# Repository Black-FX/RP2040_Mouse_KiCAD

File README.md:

# RP2040_Mouse_KiCAD
This is the hardware side of an RP2040 USB to Quadrature mouse adaptor used with retro computers, the software is available at https://github.com/Black-FX/RP2040_Mouse

A PDF of the scematic is available in [Here](PDF/scematic.pdf)

Glamour shots

# Ordering

You can order the boards here:

[PCBWay](https://www.pcbway.com/project/shareproject/RP2040_USB_Mouse_to_Quadrature_15de42f1.html)

I sell pre-assembled and programmed ones here:

[Tindie](https://www.tindie.com/products/darrens_lab/rp2040-usb-to-quadrature-mouse-adaptor/)

[EBay](https://www.ebay.com/usr/darrens_lab_nz?_trksid=p2047675.m145687.l151929)

[Trademe NZ & Aus](https://www.trademe.co.nz/a/search?member_listing=7404797&bof=McH9Ulww)

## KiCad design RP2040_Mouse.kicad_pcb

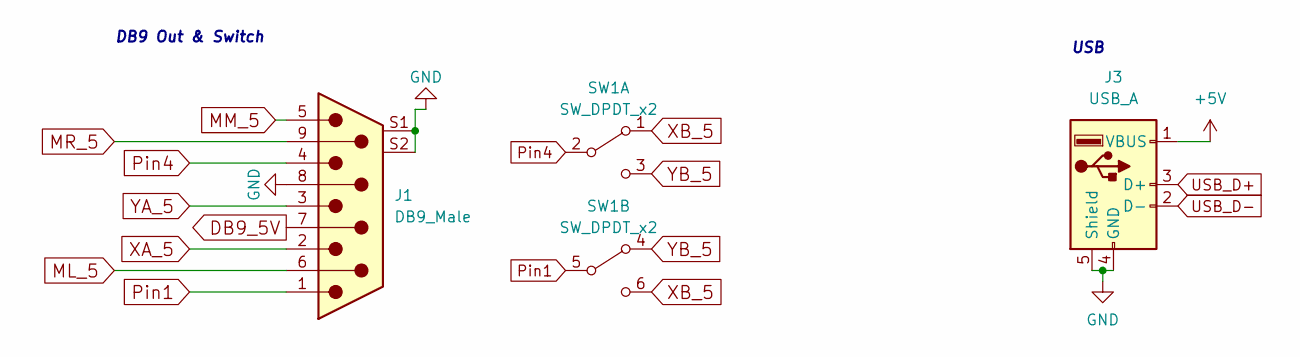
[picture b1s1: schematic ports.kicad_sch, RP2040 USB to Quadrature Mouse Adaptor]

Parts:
J1: DB9_Male; ASSMANN_A-DF_09_A_KG-T2S
J3: USB_A; USB_A_China
SW1: SW_DPDT_x2; SW_DPDT_CK_JS202011JCQN

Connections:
+5V: J3.1 (VBUS); also elsewhere on the board
DB9_5V: J1.7; also elsewhere on the board
GND: J1.8, J1.S1, J1.S2, J3.4 (GND), J3.5 (Shield); also elsewhere on the board
ML_5: J1.6; also elsewhere on the board
MM_5: J1.5; also elsewhere on the board
MR_5: J1.9; also elsewhere on the board
Pin1: J1.1, SW1.5 (B)
Pin4: J1.4, SW1.2 (B)
USB_D+: J3.3 (D+); also elsewhere on the board
USB_D-: J3.2 (D-); also elsewhere on the board
XA_5: J1.2; also elsewhere on the board
XB_5: SW1.1 (A), SW1.6 (C); also elsewhere on the board
YA_5: J1.3; also elsewhere on the board
YB_5: SW1.3 (C), SW1.4 (A); also elsewhere on the board

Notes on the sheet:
USB
DB9 Out & Switch

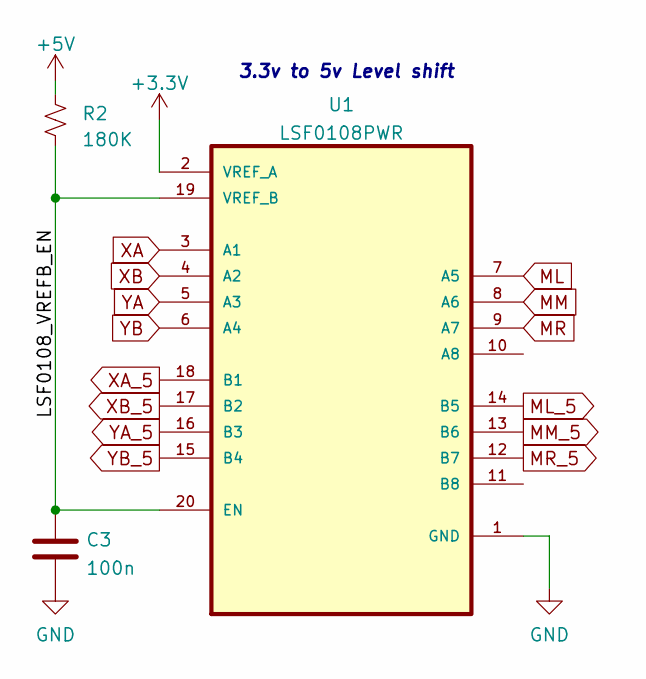
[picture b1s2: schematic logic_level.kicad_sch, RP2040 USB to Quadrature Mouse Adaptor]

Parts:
C3: 100n; C_0402_1005Metric
R2: 180K; R_0402_1005Metric
U1: LSF0108PWR; TSSOP-20_4.4x6.5mm_P0.65mm

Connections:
+3V3: U1.2 (VREF_A); also elsewhere on the board
+5V: R2.1; also elsewhere on the board
/Logic Level Shift/LSF0108_VREFB_EN: C3.1, R2.2, U1.19 (VREF_B), U1.20 (EN)
GND: C3.2, U1.1 (GND); also elsewhere on the board
ML: U1.7 (A5); also elsewhere on the board
ML_5: U1.14 (B5); also elsewhere on the board
MM: U1.8 (A6); also elsewhere on the board
MM_5: U1.13 (B6); also elsewhere on the board
MR: U1.9 (A7); also elsewhere on the board
MR_5: U1.12 (B7); also elsewhere on the board
XA: U1.3 (A1); also elsewhere on the board
XA_5: U1.18 (B1); also elsewhere on the board
XB: U1.4 (A2); also elsewhere on the board
XB_5: U1.17 (B2); also elsewhere on the board
YA: U1.5 (A3); also elsewhere on the board
YA_5: U1.16 (B3); also elsewhere on the board
YB: U1.6 (A4); also elsewhere on the board
YB_5: U1.15 (B4); also elsewhere on the board

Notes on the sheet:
3.3v to 5v Level shift

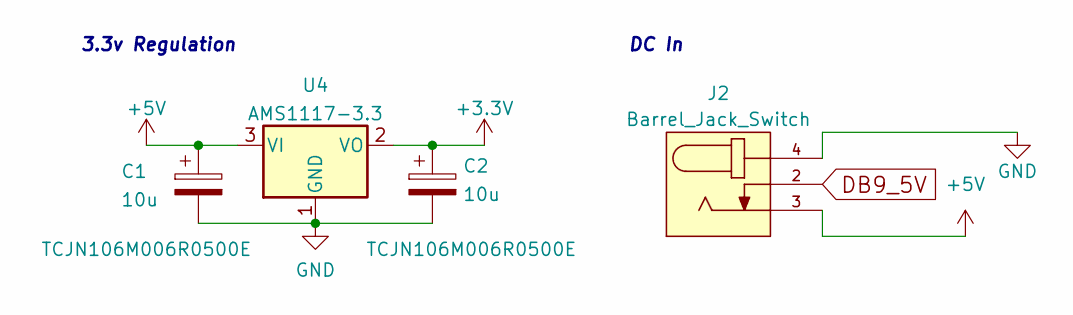
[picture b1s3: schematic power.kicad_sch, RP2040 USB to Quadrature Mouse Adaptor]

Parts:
C1, C2: 10u; C_0805_2012Metric; Part TCJN106M006R0500E
J2: Barrel_Jack_Switch; NINIGI_DC-005
U4: AMS1117-3.3; SOT-223-3_TabPin2

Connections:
+3V3: C2.1, U4.2 (VO); also elsewhere on the board
+5V: C1.1, J2.3, U4.3 (VI); also elsewhere on the board
DB9_5V: J2.2; also elsewhere on the board
GND: C1.2, C2.2, J2.4, U4.1 (GND); also elsewhere on the board

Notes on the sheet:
3.3v Regulation
DC In

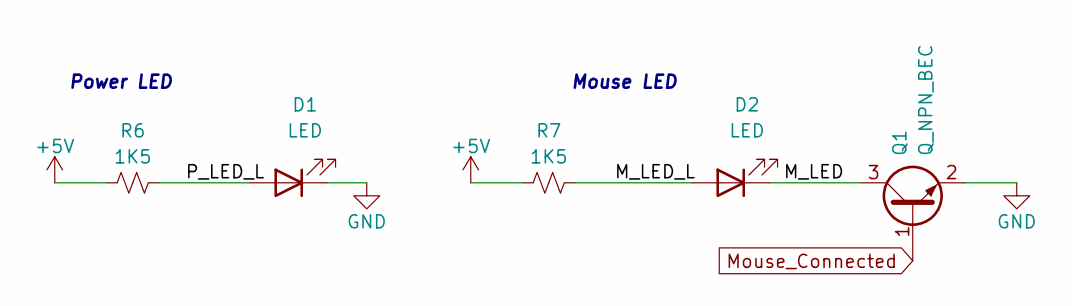
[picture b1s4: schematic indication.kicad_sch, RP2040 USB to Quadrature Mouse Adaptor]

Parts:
D1, D2: LED; LED_0603_1608Metric
Q1: Q_NPN_BEC; SOT-23-3
R6, R7: 1K5; R_0402_1005Metric

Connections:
+5V: R6.1, R7.1; also elsewhere on the board
/Indication/M_LED: D2.1 (K), Q1.3 (C)
/Indication/M_LED_L: D2.2 (A), R7.2
/Indication/P_LED_L: D1.2 (A), R6.2
GND: D1.1 (K), Q1.2 (E); also elsewhere on the board
Mouse_Connected: Q1.1 (B); also elsewhere on the board

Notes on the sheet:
Mouse LED
Power LED

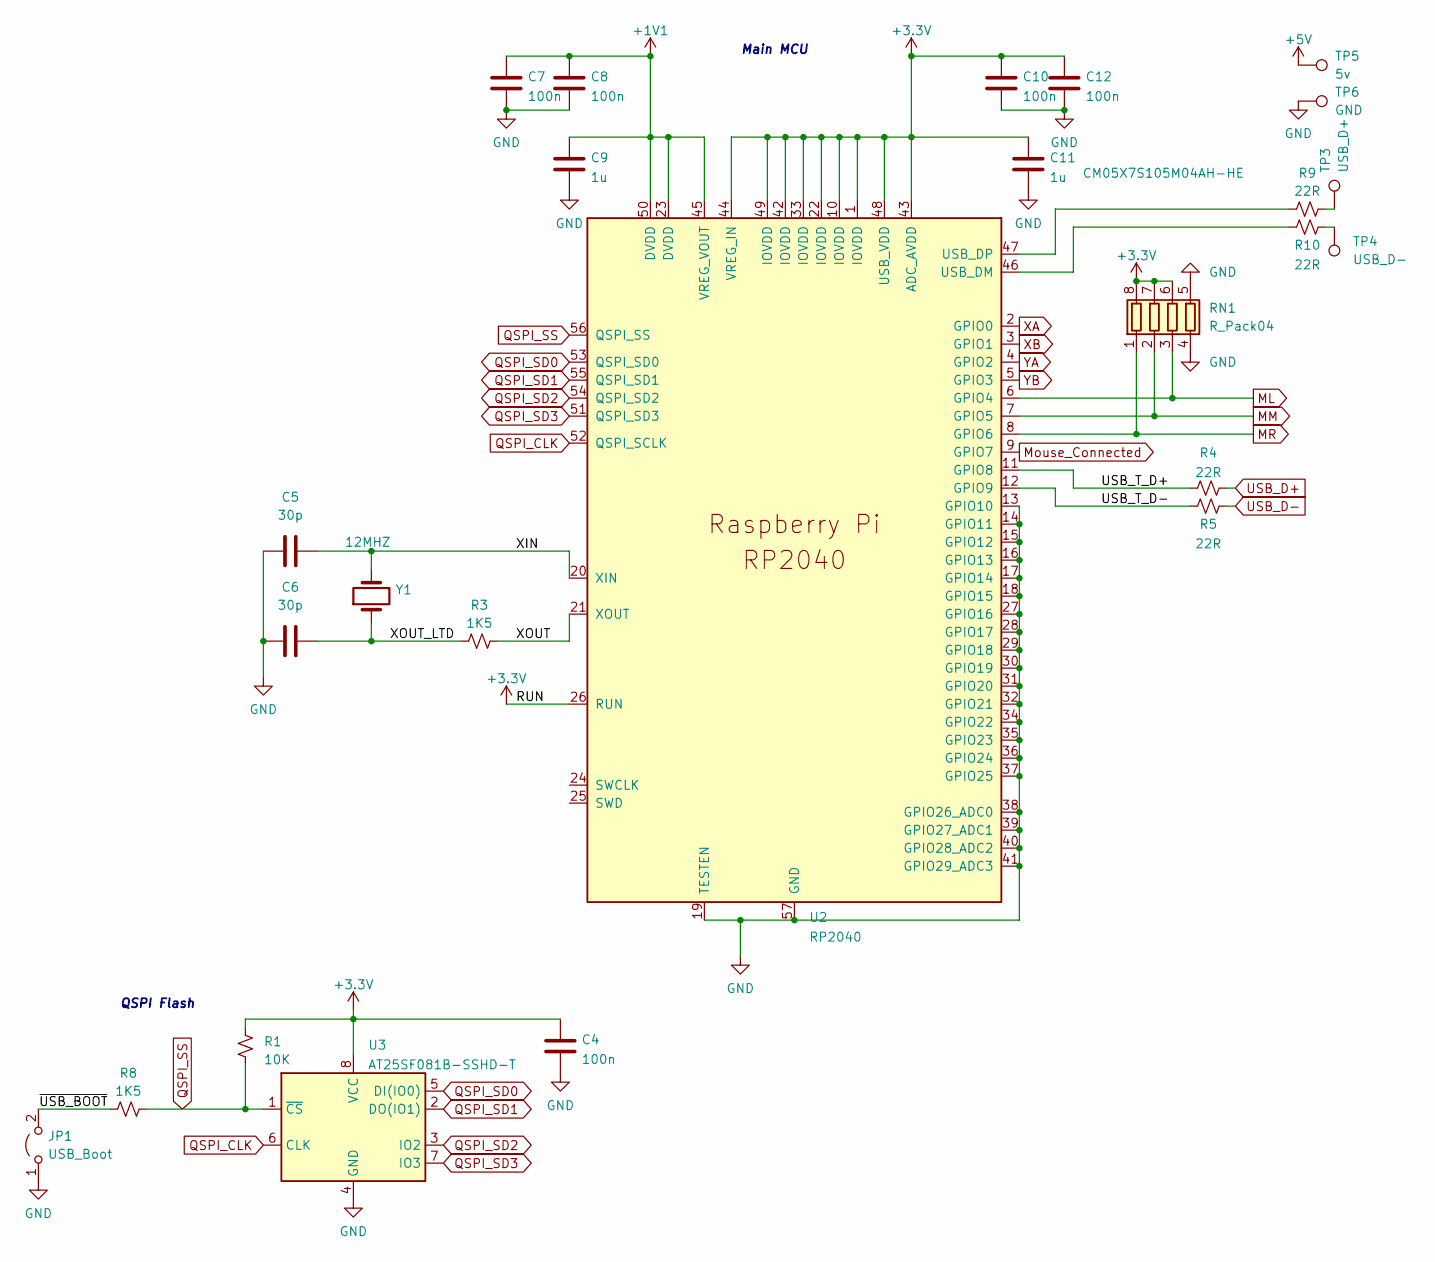
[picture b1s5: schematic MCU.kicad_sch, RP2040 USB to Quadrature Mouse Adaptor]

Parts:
C4, C7, C8, C10, C12: 100n; C_0402_1005Metric
C5, C6: 30p; C_0402_1005Metric
C9: 1u; C_0402_1005Metric
C11: 1u; C_0402_1005Metric; Part CM05X7S105M04AH-HE
JP1: USB_Boot; PinHeader_1x02_P1.27mm_Vertical
R1: 10K; R_0402_1005Metric
R3, R8: 1K5; R_0402_1005Metric
R4, R5, R9, R10: 22R; R_0402_1005Metric
RN1: R_Pack04; R_Array_Concave_4x0402
TP3: USB_D+; TestPoint_Pad_D1.0mm
TP4: USB_D-; TestPoint_Pad_D1.0mm
TP5: 5v; TestPoint_Pad_D1.0mm
TP6: GND; TestPoint_Pad_D1.0mm
U2: RP2040; RP2040-QFN-56
U3: AT25SF081B-SSHD-T; SOIC-8-1EP_3.9x4.9mm_P1.27mm_EP2.29x3mm
Y1: 12MHZ; Crystal_SMD_5032-2Pin_5.0x3.2mm

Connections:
+1V1: C7.1, C8.1, C9.1, U2.23 (DVDD), U2.45 (VREG_VOUT), U2.50 (DVDD)
+3V3: C4.1, C10.1, C11.1, C12.1, R1.1, RN1.6 (R3.2), RN1.7 (R2.2), RN1.8 (R1.2), U2.1 (IOVDD), U2.10 (IOVDD), U2.22 (IOVDD), U2.26 (RUN), U2.33 (IOVDD), U2.42 (IOVDD), U2.43 (ADC_AVDD), U2.44 (VREG_IN), U2.48 (USB_VDD), U2.49 (IOVDD), U3.8 (VCC); also elsewhere on the board
+5V: TP5.1; also elsewhere on the board
/Microcontroller/USB_T_D+: R4.1, U2.11 (GPIO8)
/Microcontroller/USB_T_D-: R5.2, U2.12 (GPIO9)
/Microcontroller/XIN: C5.2, U2.20 (XIN), Y1.2
/Microcontroller/XOUT: R3.2, U2.21 (XOUT)
/Microcontroller/XOUT_LTD: C6.2, R3.1, Y1.1
/Microcontroller/~USB_BOOT: JP1.2 (B), R8.1
GND: C4.2, C5.1, C6.1, C7.2, C8.2, C9.2, C10.2, C11.2, C12.2, JP1.1 (A), RN1.4 (R4.1), RN1.5 (R4.2), TP6.1, U2.13 (GPIO10), U2.14 (GPIO11), U2.15 (GPIO12), U2.16 (GPIO13), U2.17 (GPIO14), U2.18 (GPIO15), U2.19 (TESTEN), U2.27 (GPIO16), U2.28 (GPIO17), U2.29 (GPIO18), U2.30 (GPIO19), U2.31 (GPIO20), U2.32 (GPIO21), U2.34 (GPIO22), U2.35 (GPIO23), U2.36 (GPIO24), U2.37 (GPIO25), U2.38 (GPIO26_ADC0), U2.39 (GPIO27_ADC1), U2.40 (GPIO28_ADC2), U2.41 (GPIO29_ADC3), U2.57 (GND), U3.4 (GND); also elsewhere on the board
ML: RN1.3 (R3.1), U2.6 (GPIO4); also elsewhere on the board
MM: RN1.2 (R2.1), U2.7 (GPIO5); also elsewhere on the board
MR: RN1.1 (R1.1), U2.8 (GPIO6); also elsewhere on the board
Mouse_Connected: U2.9 (GPIO7); also elsewhere on the board
unnamed: R9.2, TP3.1
unnamed: R10.1, TP4.1
unnamed: R10.2, U2.46 (USB_DM)
unnamed: R9.1, U2.47 (USB_DP)
QSPI_CLK: U2.52 (QSPI_SCLK), U3.6 (CLK)
QSPI_SD0: U2.53 (QSPI_SD0), U3.5 (DI(IO0))
QSPI_SD1: U2.55 (QSPI_SD1), U3.2 (DO(IO1))
QSPI_SD2: U2.54 (QSPI_SD2), U3.3 (IO2)
QSPI_SD3: U2.51 (QSPI_SD3), U3.7 (IO3)
QSPI_SS: R1.2, R8.2, U2.56 (QSPI_SS), U3.1 (~CS)
USB_D+: R4.2; also elsewhere on the board
USB_D-: R5.1; also elsewhere on the board
XA: U2.2 (GPIO0); also elsewhere on the board
XB: U2.3 (GPIO1); also elsewhere on the board
YA: U2.4 (GPIO2); also elsewhere on the board
YB: U2.5 (GPIO3); also elsewhere on the board

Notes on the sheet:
Main MCU
QSPI Flash

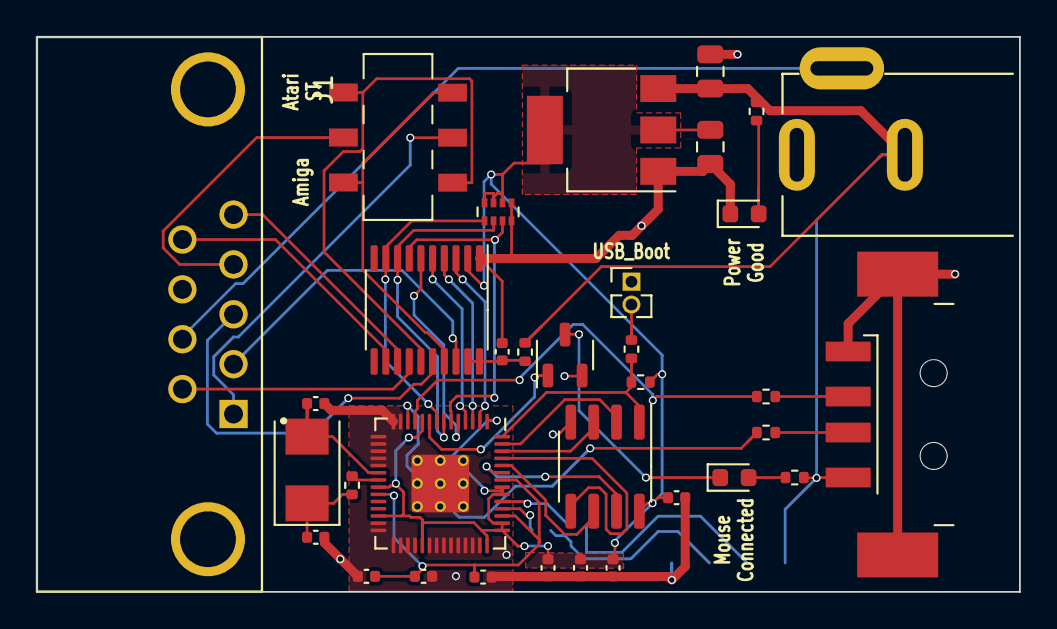
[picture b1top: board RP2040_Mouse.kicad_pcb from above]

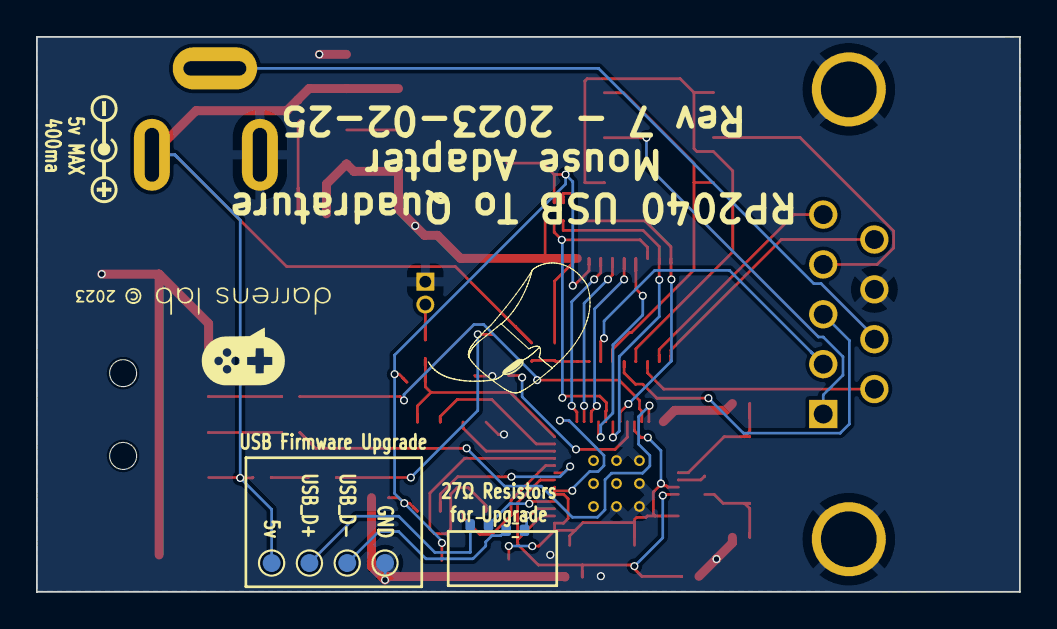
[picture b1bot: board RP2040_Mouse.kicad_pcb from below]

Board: 2 copper layers, 54.6 x 30.8 mm, 40 parts (6 on the bottom side), 44 nets.

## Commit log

2023-01-03 Inital commit
2023-01-03 Tidy up file locations
2023-01-03 Clean up unused files
2023-01-03 Add licence in preparation to open source
2023-01-03 Update license
2023-01-08 Added pullup resistors on mouse buttons, added breakout points for user software updates
2023-01-12 New board not using default USB pins
2023-01-14 Rev 4, swap the USB pins around to match the requirements of Tinyusb. Add PDF scematic Update 3d renders
2023-01-14 Generate BOM Crop images
2023-01-14 Remove lock file
2023-01-16 Updated images and board
2023-01-16 Merging local branches
2023-01-21 Fix footprint issue from 2nd PCB run, pannelize for prod, new pics, new label
2023-01-21 New PDF
2023-01-21 Upgrade to KiCAD 6.99 (Nightly)
2023-01-21 Update gitignore
2023-01-21 Break up schematic into hierarchical sheets
2023-02-03 Rev 5 update
2023-02-24 Rev 6
    Fully rerouted the board to make it cheaper and easier to make at PCBWay

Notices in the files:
RP2040_Mouse.kicad_pcb:
© 2023
